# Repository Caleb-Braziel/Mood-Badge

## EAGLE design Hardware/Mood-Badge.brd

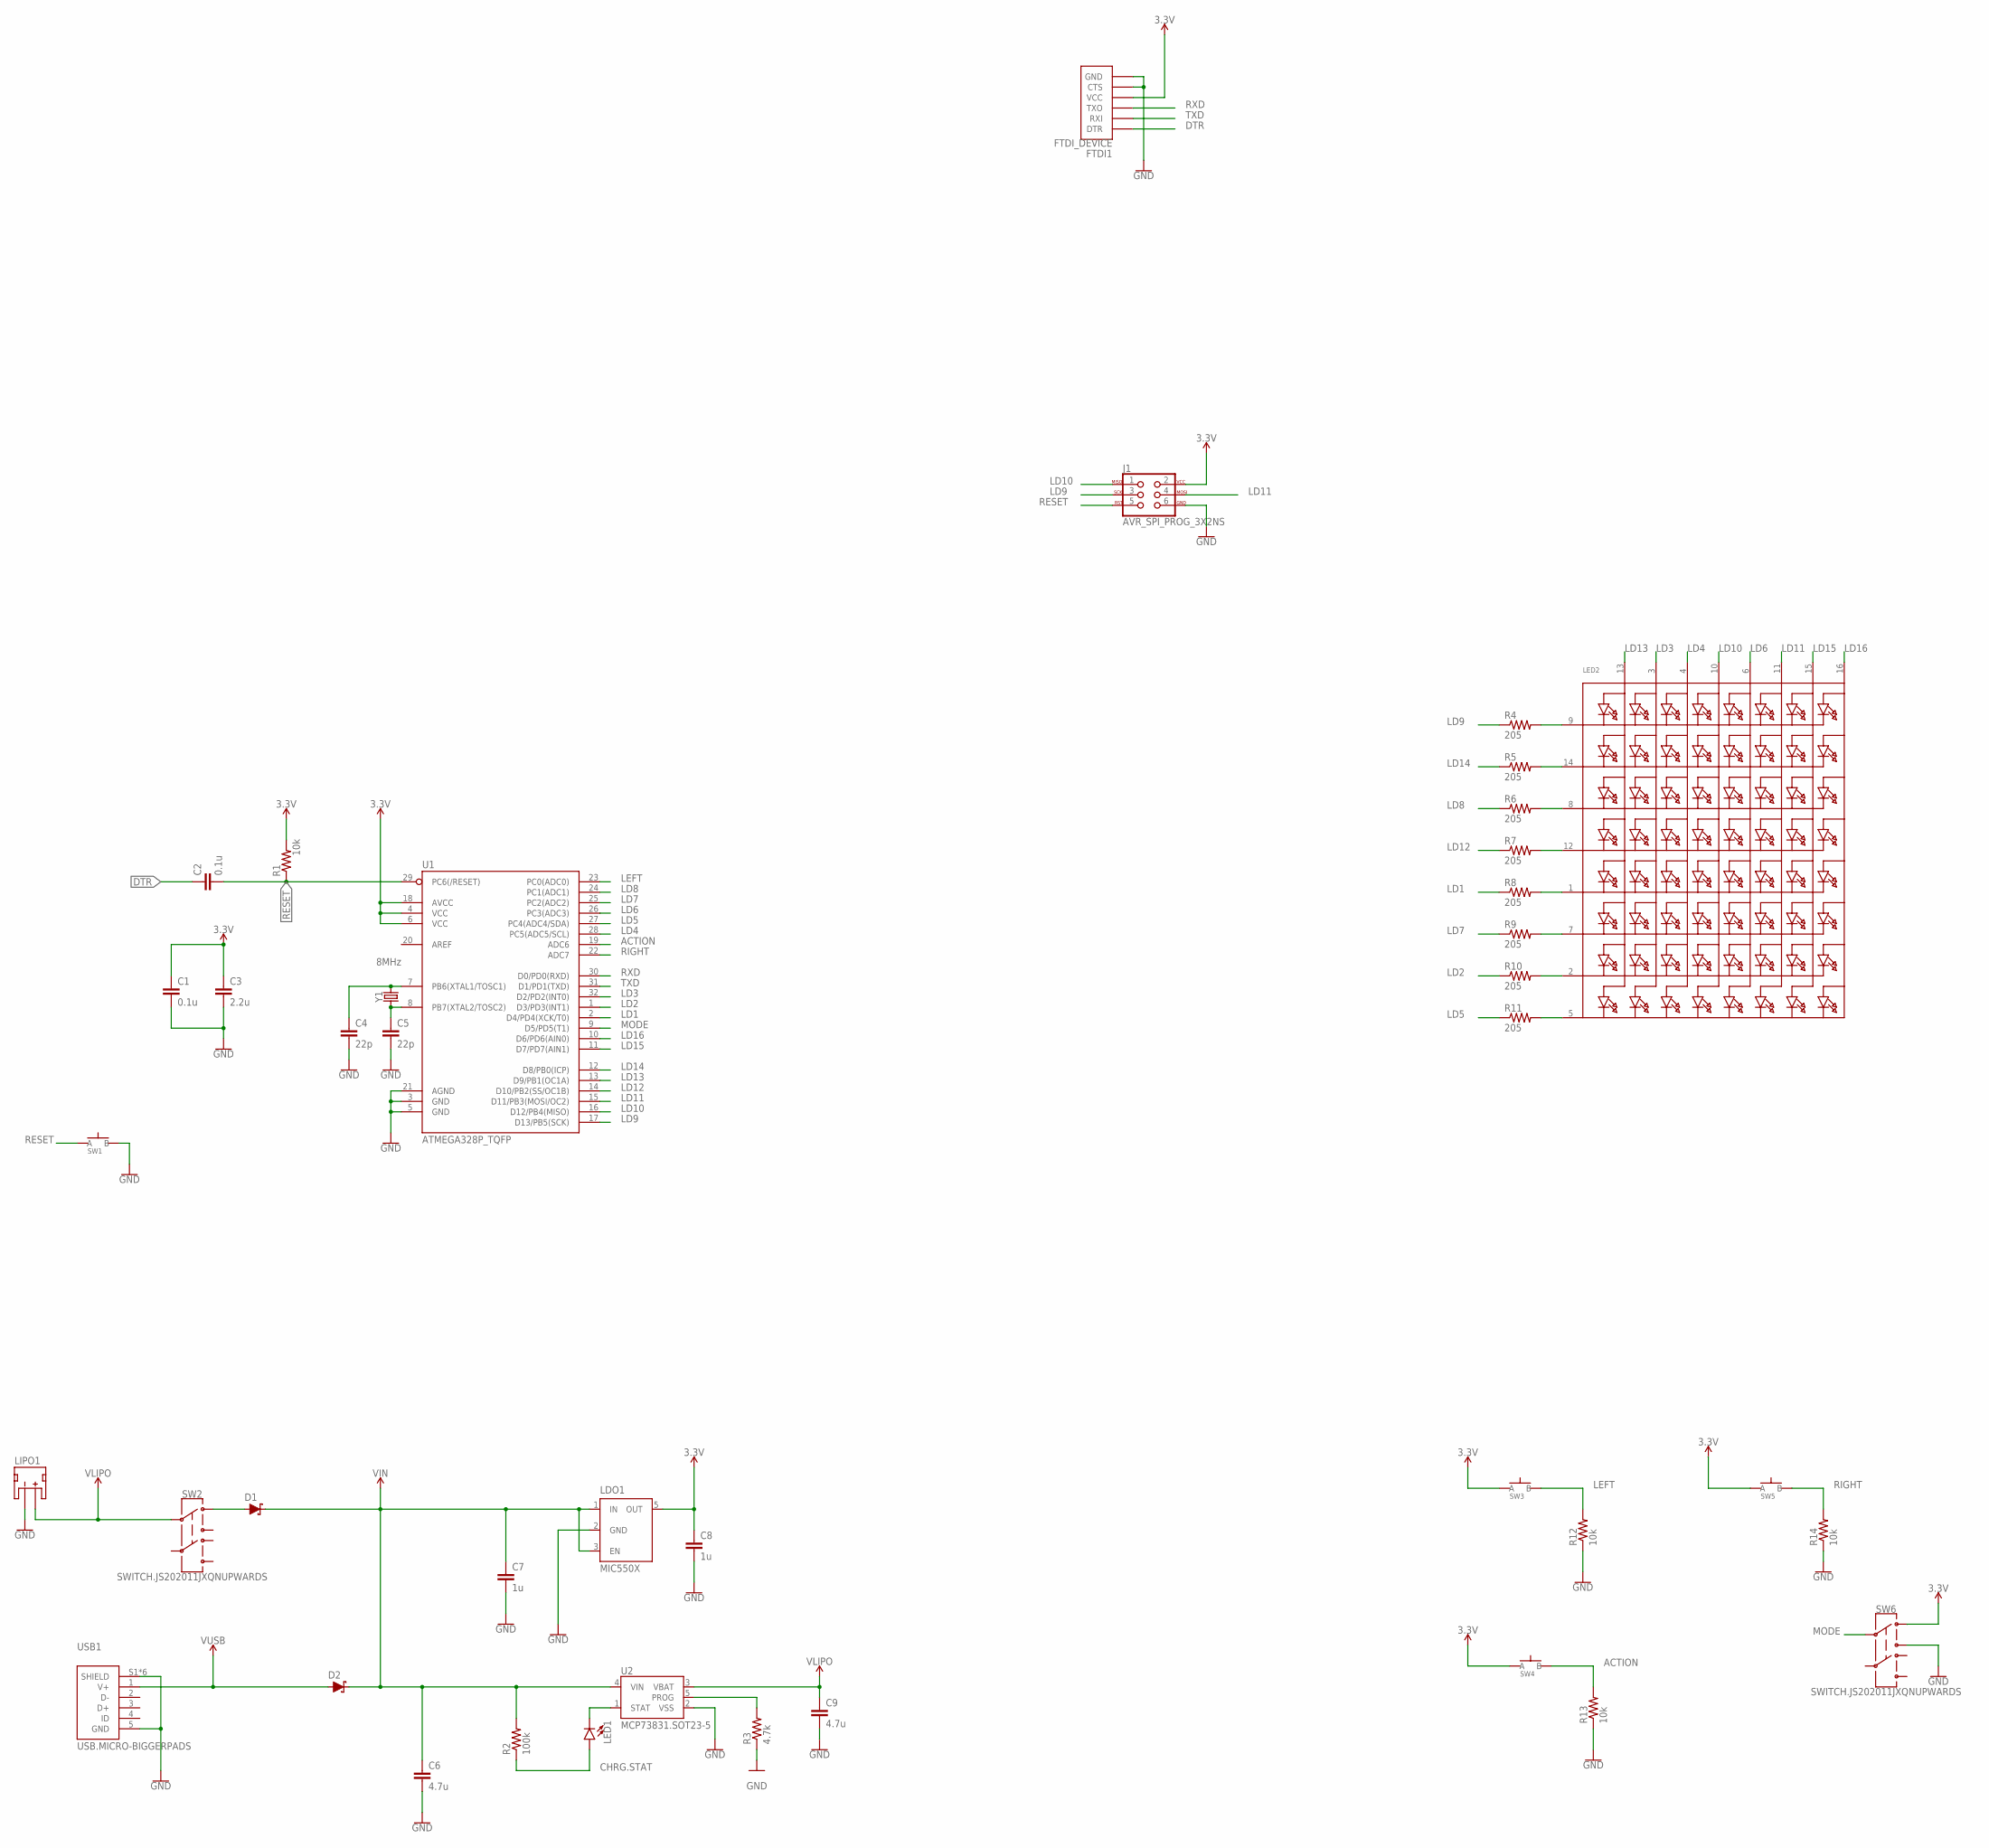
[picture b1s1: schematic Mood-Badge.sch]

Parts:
C1, C2: 0.1u; C0603
C3: 2.2u; C0603
C4, C5: 22p; C0603
C6, C9: 4.7u; C0603
C7, C8: 1u; C0603
D1, D2: SCHOTTKY-USC; USC
FTDI1: FTDI_DEVICE
J1: AVR_SPI_PROG_3X2NS; 2X3-NS
LDO1: MIC550X; SOT23-5
LED1: LED0603; LED-0603
LED2: DOTMATRIX_8X8_ROWCATHODEM12A881UR; DOTMATRIX_BL-M12A881UR
LIPO1: JST_2MM_MALE; JST-2-SMD
R1, R12, R13, R14: 10k; R0603
R2: 100k; R0603
R3: 4.7k; R0603
R4, R5, R6, R7, R8, R9, R10, R11: 205; R0603
SW1, SW3, SW4, SW5: SPST.KT11P4SM34LFS
SW2, SW6: SWITCH.JS202011JXQNUPWARDS; SWITCH.00
U1: ATMEGA328P_TQFP; TQFP32-08
U2: MCP73831.SOT23-5; SOT23-5
USB1: USB.MICRO-BIGGERPADS; USB-MICRO-01.BIGGERPADS
Y1: 8MHz; CA-301

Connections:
3.3V: C1.1, C3.1, C8.1, FTDI1.VCC, J1.2, LDO1.5 (OUT), R1.2, SW3.1 (A), SW3.2 (A), SW4.1 (A), SW4.2 (A), SW5.1 (A), SW5.2 (A), SW6.1, U1.4 (VCC), U1.6 (VCC), U1.18 (AVCC)
ACTION: R13.2, SW4.3 (B), SW4.4 (B), U1.19 (ADC6)
CHRG.STAT: LED1.A, R2.1
DTR: C2.1, FTDI1.DTR
GND: C1.2, C3.2, C4.2, C5.2, C6.2, C7.2, C8.2, C9.2, FTDI1.CTS, FTDI1.GND, J1.6, LDO1.2 (GND), LIPO1.1 (-), R3.1, R12.1, R13.1, R14.1, SW1.3 (B), SW1.4 (B), SW6.3, U1.3 (GND), U1.5 (GND), U1.21 (AGND), U2.2 (VSS), USB1.5 (GND), USB1.S1 (SHIELD), USB1.S2 (SHIELD), USB1.S3 (SHIELD), USB1.S4 (SHIELD), USB1.S5 (SHIELD), USB1.S6 (SHIELD)
LD1: R8.1, U1.2 (D4/PD4(XCK/T0))
LD2: R10.1, U1.1 (D3/PD3(INT1))
LD3: LED2.3 (A2), U1.32 (D2/PD2(INT0))
LD4: LED2.4 (A3), U1.28 (PC5(ADC5/SCL))
LD5: R11.1, U1.27 (PC4(ADC4/SDA))
LD6: LED2.6 (A5), U1.26 (PC3(ADC3))
LD7: R9.1, U1.25 (PC2(ADC2))
LD8: R6.1, U1.24 (PC1(ADC1))
LD9: J1.3, R4.1, U1.17 (D13/PB5(SCK))
LD10: J1.1, LED2.10 (A4), U1.16 (D12/PB4(MISO))
LD11: J1.4, LED2.11 (A6), U1.15 (D11/PB3(MOSI/OC2))
LD12: R7.1, U1.14 (D10/PB2(SS/OC1B))
LD13: LED2.13 (A1), U1.13 (D9/PB1(OC1A))
LD14: R5.1, U1.12 (D8/PB0(ICP))
LD15: LED2.15 (A7), U1.11 (D7/PD7(AIN1))
LD16: LED2.16 (A8), U1.10 (D6/PD6(AIN0))
LEFT: R12.2, SW3.3 (B), SW3.4 (B), U1.23 (PC0(ADC0))
MODE: SW6.2, U1.9 (D5/PD5(T1))
unnamed: C4.1, U1.7 (PB6(XTAL1/TOSC1)), Y1.2
unnamed: C5.1, U1.8 (PB7(XTAL2/TOSC2)), Y1.1
unnamed: LED1.C, U2.1 (STAT)
unnamed: LED2.2 (K7), R10.2
unnamed: LED2.5 (K8), R11.2
unnamed: LED2.7 (K6), R9.2
unnamed: LED2.1 (K5), R8.2
unnamed: LED2.12 (K4), R7.2
unnamed: LED2.8 (K3), R6.2
unnamed: LED2.14 (K2), R5.2
unnamed: LED2.9 (K1), R4.2
unnamed: D1.+ (A), SW2.1
unnamed: R3.2, U2.5 (PROG)
RESET: C2.2, J1.5, R1.1, SW1.1 (A), SW1.2 (A), U1.29 (PC6(/RESET))
RIGHT: R14.2, SW5.3 (B), SW5.4 (B), U1.22 (ADC7)
RXD: FTDI1.RXI (TXO), U1.30 (D0/PD0(RXD))
TXD: FTDI1.TXO (RXI), U1.31 (D1/PD1(TXD))
VIN: C6.1, C7.1, D1.- (C), D2.- (C), LDO1.1 (IN), LDO1.3 (EN), R2.2, U2.4 (VIN)
VLIPO: C9.1, LIPO1.2 (+), SW2.2, U2.3 (VBAT)
V_USB: D2.+ (A), USB1.1 (V+)

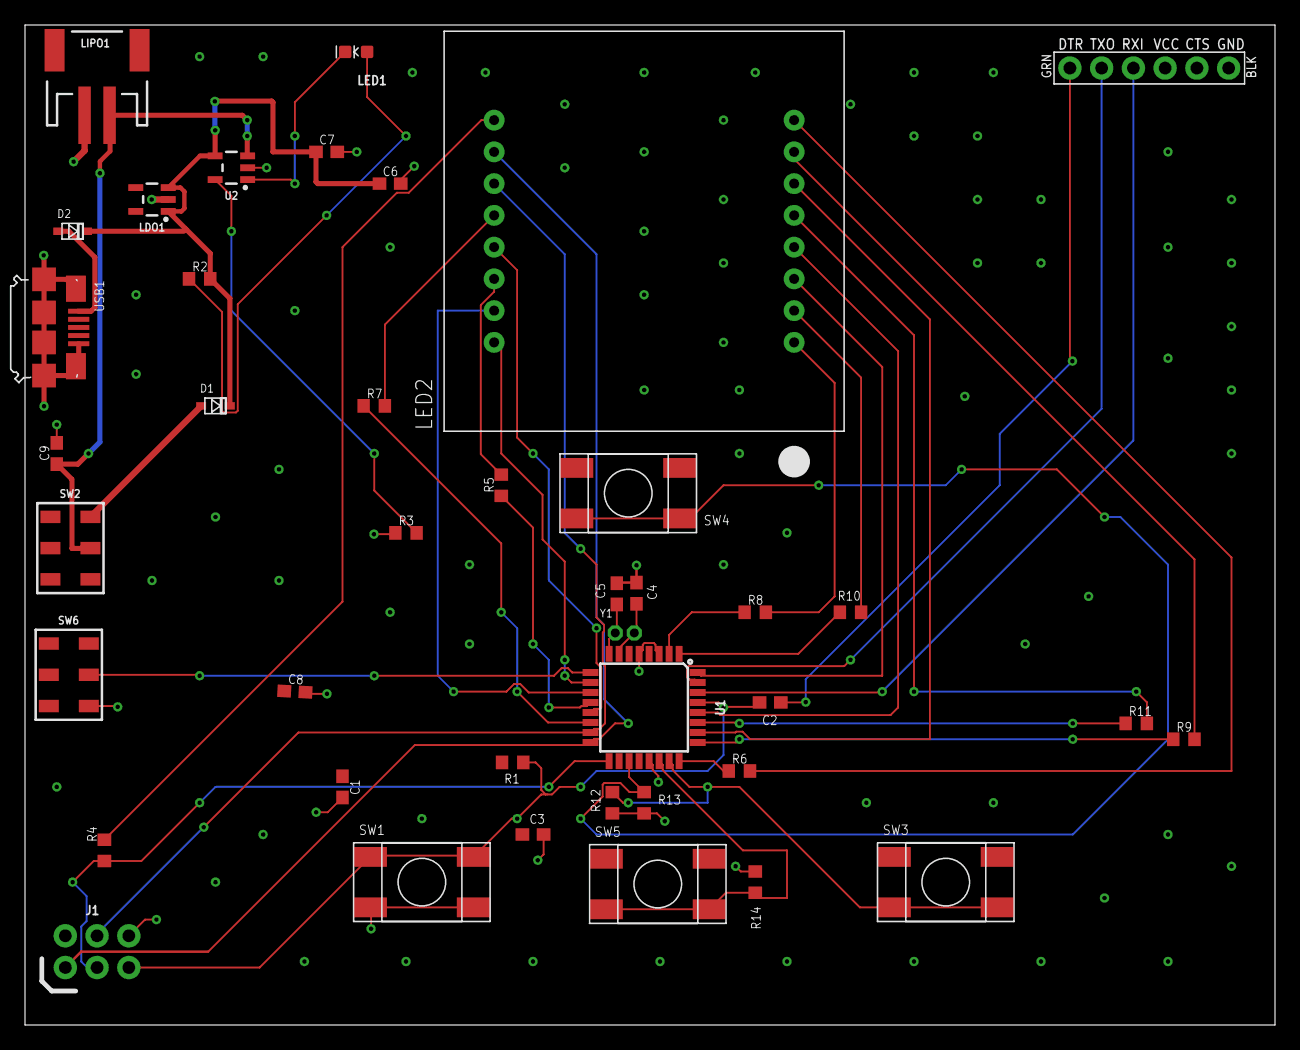
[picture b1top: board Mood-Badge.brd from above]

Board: 2 copper layers, 100.0 x 80.0 mm, 41 parts (0 on the bottom side), 43 nets.

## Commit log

2022-09-08 added some random file teacher told me to add
2022-09-14 Hardware
2022-09-14 Firmware
2022-09-15 made some progress on schematic
2022-09-21 Updated sch and brd
2022-10-05 hardware update
2022-10-17 Hardware/Mood-badge.brd
2022-11-02 New BOM
2022-11-19 orlando made changes and ordered boards
